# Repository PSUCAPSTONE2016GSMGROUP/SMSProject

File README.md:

# SMSProject

This is a test of adding some code to the initial README.md file in the "master" branch.
Changes are being made in the readme-edits branch which was just created.

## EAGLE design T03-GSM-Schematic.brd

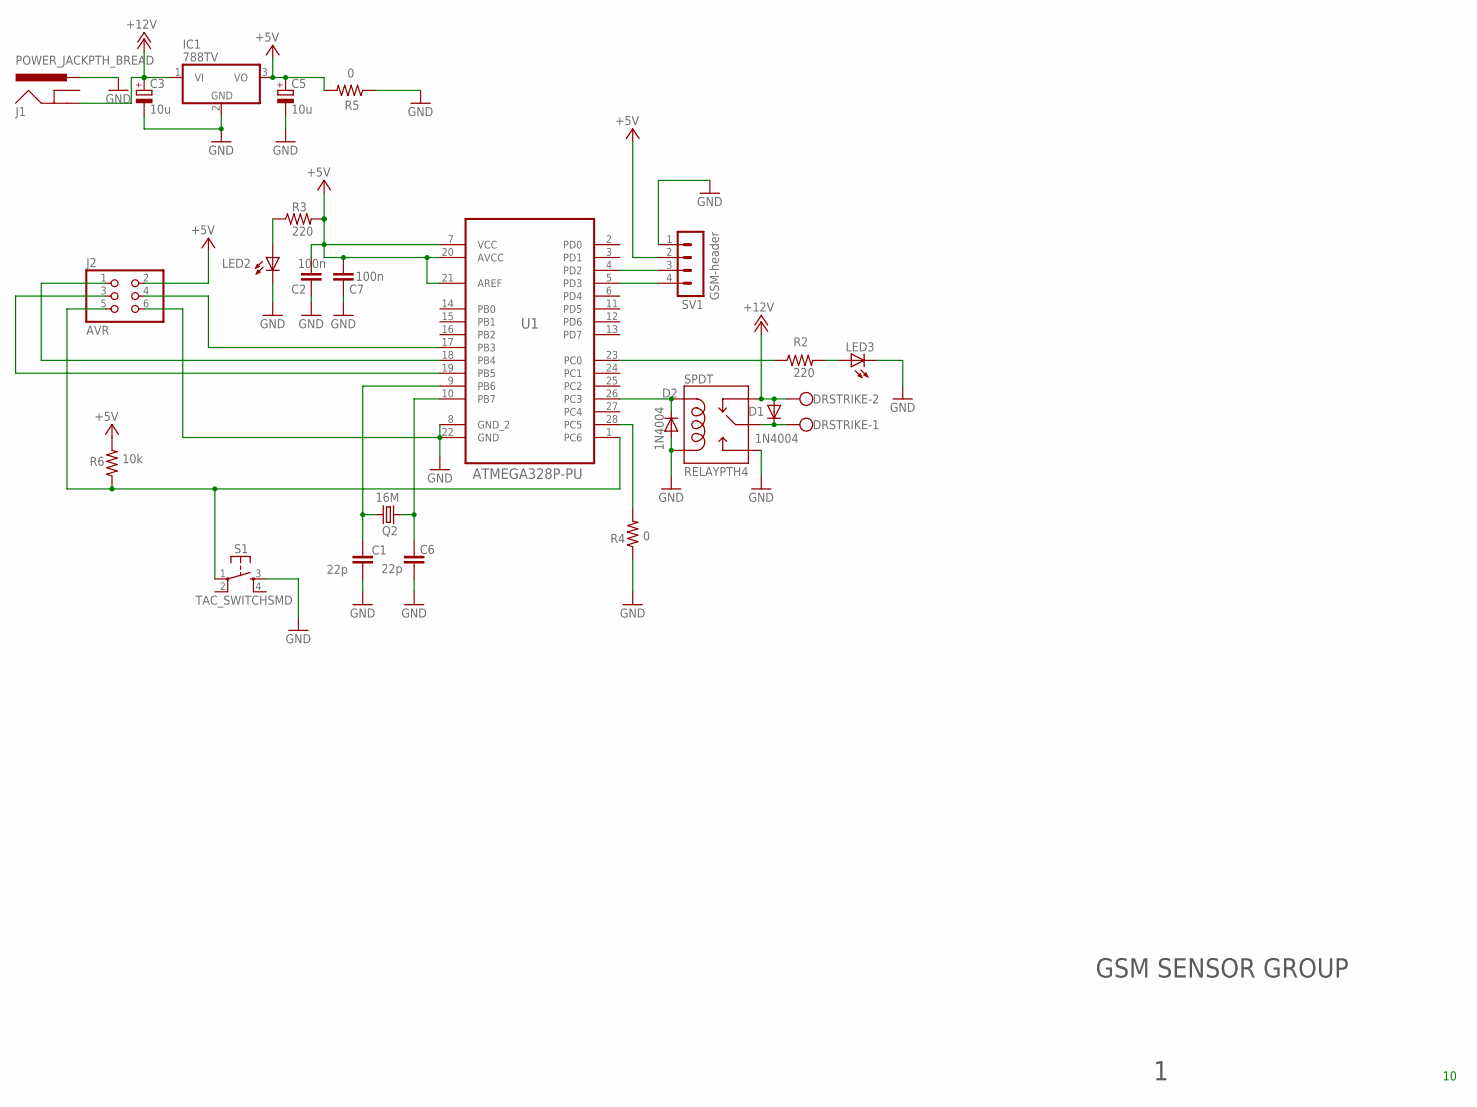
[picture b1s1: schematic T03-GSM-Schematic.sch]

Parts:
C1, C6: 22p; C0603
C2, C7: 100n; C0603
C3, C5: 10u; E5-10,5
D1, D2: 1N4004; DO41-10
DRSTRIKE: W237-102
IC1: 788TV; TO220V
J1: POWER_JACKPTH_BREAD; POWER_JACK_PTH_BREAD
J2: AVR; 2X03
LED2: LEDSML0603; SML0603
LED3: LED5MM
Q2: 16M; HC49UP
R2, R3: 220; R0603
R4, R5: 0; 0204/5
R6: 10k; R0603
S1: TAC_SWITCHSMD; TACTILE-SWITCH-SMD
SPDT: RELAYPTH4; RELAY-JZC
SV1: GSM-header; MA04-1
U1: ATMEGA328P-PU; DIP254P762X457-28

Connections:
+5V: C2.2, C5.+, C7.2, IC1.3 (VO), J2.2, R3.2, R5.2, R6.2, SV1.2, U1.7 (VCC), U1.20 (AVCC), U1.21 (AREF)
+12V: C3.+, D1.A, DRSTRIKE.2, IC1.1 (VI), J1.GND, SPDT.2 (NC)
GND: C1.2, C2.1, C3.-, C5.-, C6.2, C7.1, D2.A, IC1.2 (GND), J1.PWR, J2.6, LED2.C, LED3.K (C), R4.1, R5.1, S1.3, SPDT.1 (COIL2), SPDT.3 (NO), SV1.1, U1.8 (GND_2), U1.22 (GND)
unnamed: J2.5, R6.1, S1.1, U1.1 (PC6)
unnamed: LED2.A, R3.1
unnamed: D1.C, DRSTRIKE.1, SPDT.4 (MAIN)
unnamed: J2.3, U1.19 (PB5)
unnamed: LED3.A, R2.2
unnamed: J2.4, U1.17 (PB3)
unnamed: J2.1, U1.18 (PB4)
unnamed: R2.1, U1.23 (PC0)
unnamed: R4.2, U1.28 (PC5)
unnamed: D2.C, SPDT.5 (COIL1), U1.26 (PC3)
unnamed: C1.1, Q2.2, U1.9 (PB6)
unnamed: C6.1, Q2.1, U1.10 (PB7)
RX: SV1.4, U1.5 (PD3)
TX: SV1.3, U1.4 (PD2)

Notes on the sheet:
GSM SENSOR GROUP

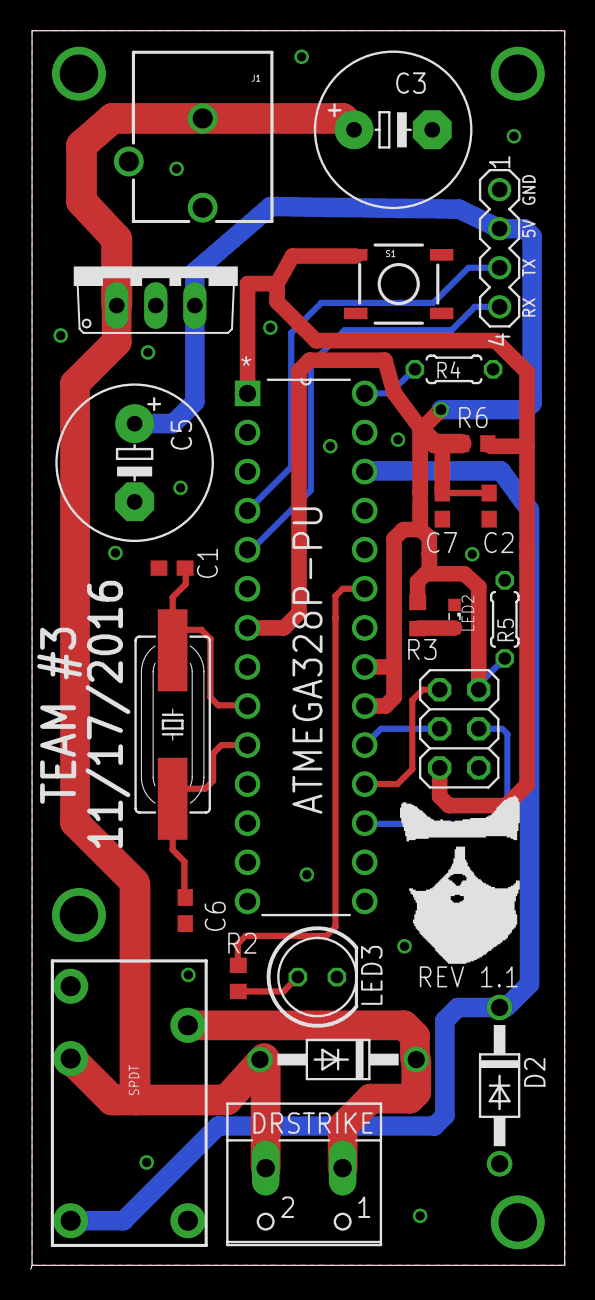
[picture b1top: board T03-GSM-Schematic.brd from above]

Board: 2 copper layers, 34.7 x 80.5 mm, 24 parts (0 on the bottom side), 17 nets.

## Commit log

2016-10-09 Update README.md
    Added a few lines to the initial README.md. Originally from the "master" branch, the changes were made withing the "readme-edits" branch.
2016-10-14 The homework 2 is already in Homework folder
2016-11-03 Cleaned up the schematic and fixed ERC errors
2016-11-05 Add files via upload
    Fixed the relay to door strike connection and replaced terminals with 237-102 WAGO terminal blocks
2016-11-07 updated the Schematic and changed PCB layout
    Updated the Schematic and included a surface mount for the Voltage regulator and changed the layout of the PCB and added a logo to it
2016-11-08 Changed the logo location and added Revision #
    DRC errors down to 49 (All of the errors are Stop Errors)
2016-11-08 Arranged names for components
2016-11-08 Fixed DRC errors - Down to 10 errors
2016-11-09 Add files via upload
    Added diode to door strike output and cleaned up breadboard lines.
    Also solved consistency errors
2016-11-09 Made board and schematic consistent - no ERC erros
2016-11-09 Fixed some DRC errors
    Down to 10 errors again
2016-11-09 timed and added mounting holes
2016-11-10 Fixed DRC errors and added dimensions
2016-11-10 Renamed file to meet the specification
2016-11-10 changed the Power Jack to through hole
2016-11-10 Being replaced with T03-GSM-Schematic.sch
2016-11-10 Switched power + and - on power jack
2016-11-13 Add files via upload
    Bill of materials: Rev. 1
2016-11-13 Add files via upload
    Prices and links to parts added.
2016-11-14 Change the Voltage regulator to through hole
2016-11-14 Fixed outline around board
2016-11-14 Gerber Files initial upload
2016-11-14 Fixed minor issue with board outline
2016-11-15 Added terminal points for GSM module
    5V and GND
2016-11-15 Moved the power jack position
2016-11-15 Gerber files for the new board layout
2016-11-15 Gerber files for latest board file
2016-11-15 Changed terminal points component
2016-11-15 Gerber files for changes i made in the layout
2016-11-15 added few missing files
2016-11-16 Add files via upload
    gnd orientation fixed.
2016-11-16 Add files via upload
    Fixed power jack pin on schematic. There is an inconsistency with the board and schematic
2016-11-16 fixed Consistency error with GSM terminal points
2016-11-16 fixed power jack connection
2016-11-16 Add files via upload
    added flyback diode, bypass caps. No board level work done yet.
2016-11-16 Changed the layout of the PCB board
2016-11-16 Add files via upload
    Added test point, fixed ERC error.
    More updates to come.
2016-11-16 Add files via upload
    Added another test point after the voltage limiter and increased line thickness on power leads
2016-11-17 Made the 5V line thicker
2016-11-17 Add files via upload
    Final Revision.
    No DRC or ERC errors.
    Updates:
    Power lines thickened
    Power capacitor orientation fixed
    Reset pull-up resistor added
2016-11-17 Made the board litter wider
2016-11-18 Add files via upload
    Updated BOM to include 0 ohm test resistors, 100n capacitors, and updated quantities of parts
2016-11-18 Delete T03-BOM.xlsx
    New updated BOM created.
2016-12-02 Add files via upload
    Added door strike, GSM Module, and power supply prices to overall cost
2016-12-04 Add files via upload
    Fixed duplicates, updated prices, added PCB cost
2016-12-05 Create LICENSE

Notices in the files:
parts and their libraries:
SparkFun-Connectors: Licensing: Creative Commons ShareAlike 4.0 International - https://creativecommons.org/licenses/by-sa/4.0
